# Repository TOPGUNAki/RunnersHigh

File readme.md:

Runners High
 
運動器具に取り付け可能なコントローラデバイス
 
# DEMO

どこのご家庭にもある、ランニングマシンやエクササイズバイクに取り付けて
PCのコントローラにするデバイスです。
 
# Features
 
ランニングマシンやエクササイズバイクなどの周期的運動する機構に非接触センサーを取り付けることで
回転数を取得し、回転数に応じてPCへキーボード出力を行います。
 
# Requirement
 
*周期的運動をする機構を持つ運動器具
*trinket m0
  
# Installation

1.ネオジム磁石を周期運動する部位に取り付け、ホールセンサー基板を磁力を検知する距離に設置します。
!注意!
ネオジム磁石には極性があります。裏表が逆だと検知しません。
磁気を検知した際にtrinket m0上のLEDが光ります。
ネオジム磁石の移動によってLEDが点滅するかを確認してください。
2.他、メインボードおよびボタンボードを適切な位置に配置し、ハーネスで接続します。
3.trinket m0とPCをusb micro Bケーブルで接続します。PCからはHIDキーボードと認識されます。
 
# Usage
 
DEMOの実行方法など、"hoge"の基本的な使い方を説明する

google streetviewでの利用例
1.google streetviewを立ち上げてアクティブにします。
2.センサーが回転を検知すると"w"キーが出力されます。(前方移動)
3.視線を左右に移動させる際は左/右ボタンを押すと"a"/"d"キーが出力されます。
4.移動量に対するwキー出力の頻度を調整するにはメイン基板上のボリュームを回すことで調整できます。
 
# Note
arduino IDEを利用し、trinket m0のコードを改変、ファームを書き換えることにより
任意のキー出力に変更することができます。

'''

//KEY config
//default value is for google map(chrome browser)

#define KEY_FOWARD 'w' //foward key
#define KEY_R 'd'      //turn right
#define KEY_L 'a'      //turn left

'''

#disclaim
当装置を利用した際における事故、PC等の損傷、および健康被害について
作成者は一切の責任を負いません。
 
# Author
 
* 作成者 あきにゃん
* E-mail aki.primary@gmail.com
* twitter @TOPGUN_Aki
 
# License

CC BY-NC 4.0

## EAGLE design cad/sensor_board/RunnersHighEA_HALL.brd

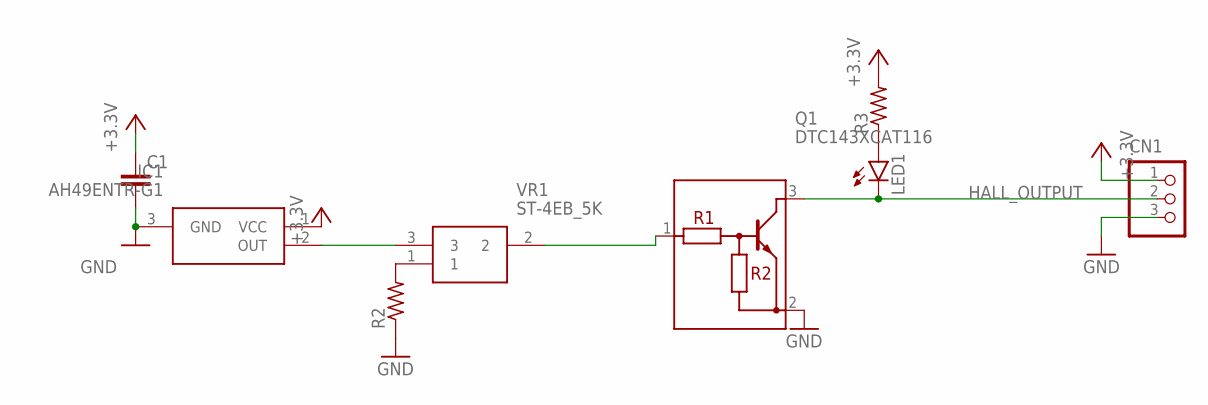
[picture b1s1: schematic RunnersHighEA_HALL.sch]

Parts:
C1: C-EUC0603; C0603
CN1: S3B-PH-SM4-TB
IC1: AH49ENTR-G1; SOT95P280X145-3N
LED1: LEDCHIP-LED0603; CHIP-LED0603
Q1: DTC143XCAT116; SOT85P240X115-3N
R2, R3: R-US_R0603; R0603
VR1: ST-4EB_5K; ST-4EB

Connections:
+3.3V: C1.1, CN1.1, IC1.1 (VCC), R3.2
GND: C1.2, CN1.3, IC1.3 (GND), Q1.2 (E), R2.1
HALL_OUTPUT: CN1.2, LED1.C, Q1.3 (C)
unnamed: R2.2, VR1.1
unnamed: IC1.2 (OUT), VR1.3
unnamed: Q1.1 (B), VR1.2
unnamed: LED1.A, R3.1

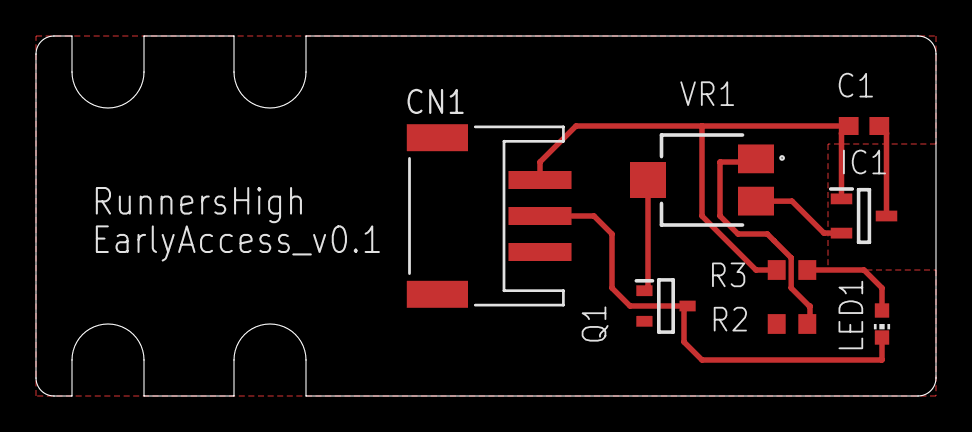
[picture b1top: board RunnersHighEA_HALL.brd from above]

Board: 2 copper layers, 50.0 x 20.0 mm, 8 parts (0 on the bottom side), 7 nets.

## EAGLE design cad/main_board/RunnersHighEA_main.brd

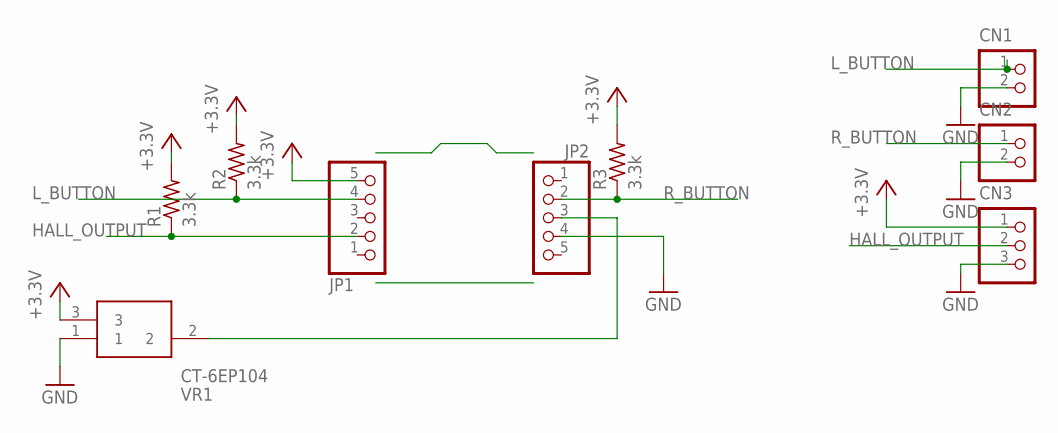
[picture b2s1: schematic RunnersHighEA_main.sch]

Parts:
CN1, CN2: S2B-PH-SM4-TB
CN3: S3B-PH-SM4-TB
JP1, JP2: PINHD-1X5; 1X05
R1, R2, R3: 3.3k; R0603
VR1: CT-6EP104; CT-6EP

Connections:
+3.3V: CN3.1, JP1.5, R1.2, R2.2, R3.2, VR1.3
GND: CN1.2, CN2.2, CN3.3, JP2.4, VR1.1
HALL_OUTPUT: CN3.2, JP1.2, R1.1
L_BUTTON: CN1.1, JP1.4, R2.1
unnamed: JP2.3, VR1.2
R_BUTTON: CN2.1, JP2.2, R3.1

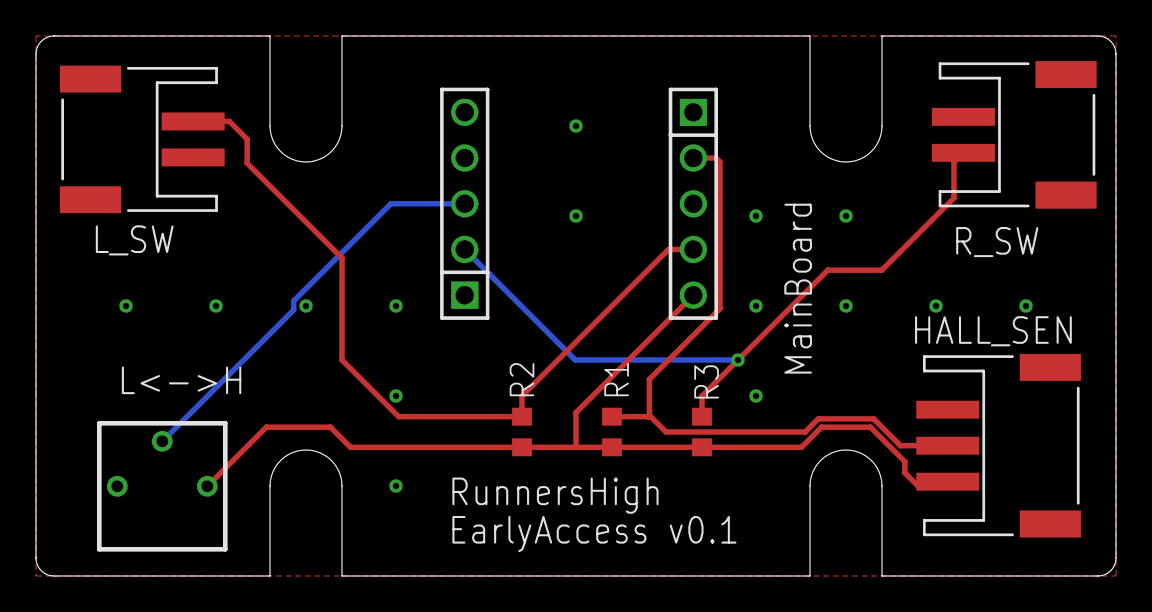
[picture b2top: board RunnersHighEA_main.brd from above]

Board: 2 copper layers, 60.0 x 30.0 mm, 9 parts (0 on the bottom side), 6 nets.

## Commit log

2020-07-02 first comit.
